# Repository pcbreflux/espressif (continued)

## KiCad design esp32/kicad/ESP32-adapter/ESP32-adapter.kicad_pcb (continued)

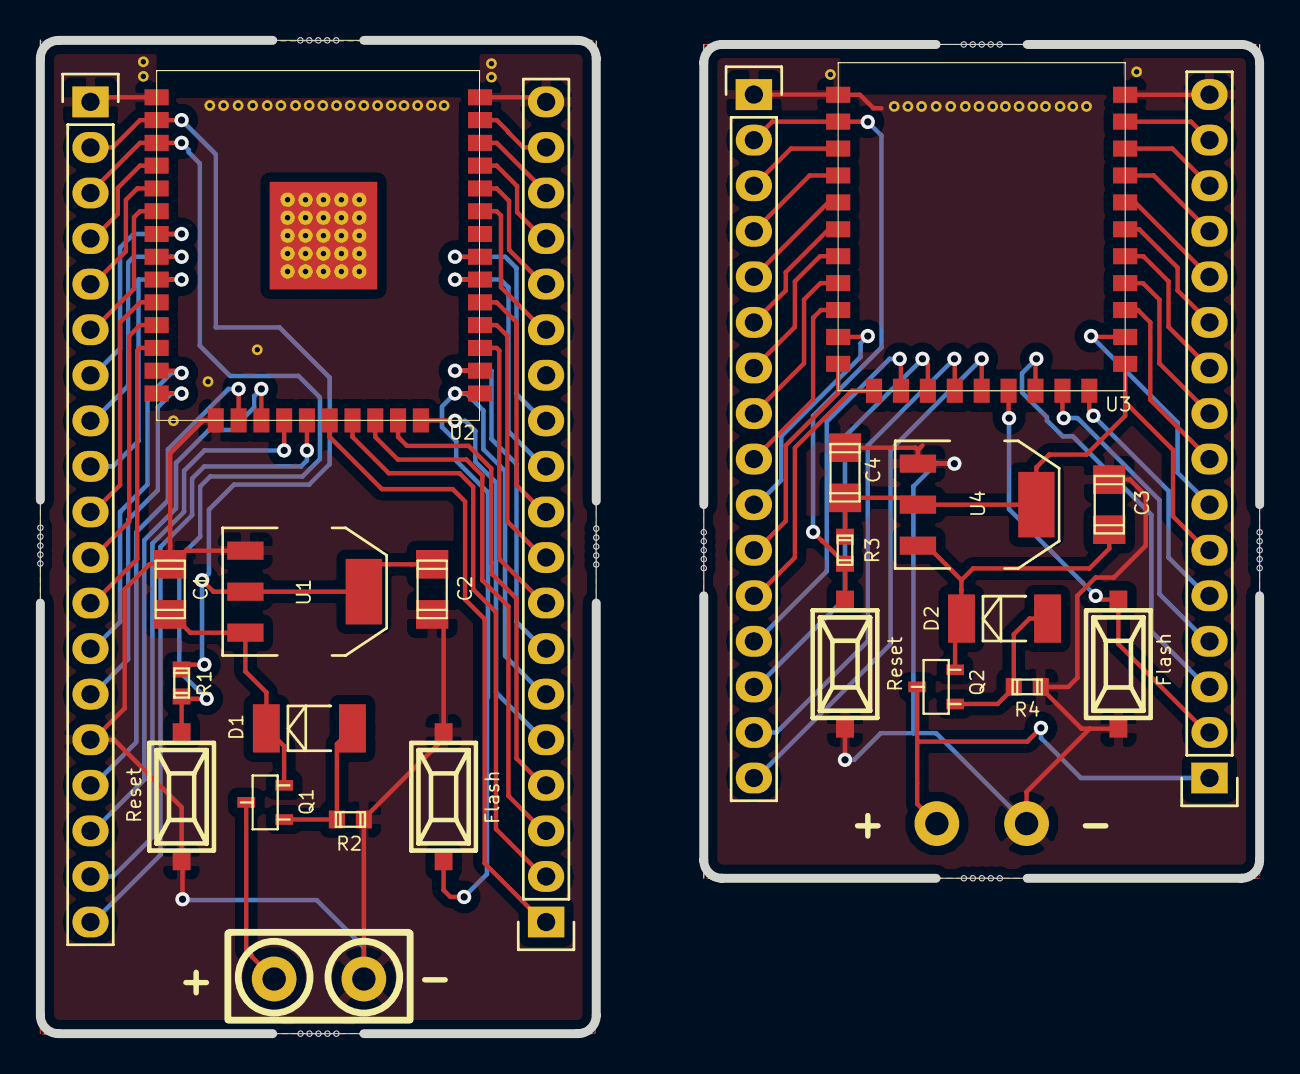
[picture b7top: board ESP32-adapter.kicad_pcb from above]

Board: 2 copper layers, 68.0 x 55.4 mm, 26 parts (1 on the bottom side), 70 nets.

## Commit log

2016-11-06 ESP32 Adapter with KiCad
2016-11-08 ESP32 Eddystone
2016-11-11 iBeacon
2016-11-20 Ucglib ESP32 port
2016-11-30 ESP32 APA102
2016-12-08 ESP32_MAX6675_thingspeak
2016-12-14 ESP32 ssl smtps gmail
2016-12-21 ESP32 u8g2 Si7021 SSD1306
2016-12-27 ESP32 DIY Radar Intrusion Detector
2016-12-30 ESP32 BLE Client with nRF51822 BLE Server
2017-01-03 ESP32 TSL v1.2 Weebserver i.e. GPIO Remetoe Controll
2017-01-04 ESP32-HELP-Button
2017-01-09 ESP32-adapter pinmap
2017-01-09 ESP32-HELP-Button assembly files
2017-01-10 esp-idf changed to bluedroid
2017-01-18 ESP32_blufi_beacon_tracker
2017-01-27 ESP32_mqtt_secure_publish
2017-02-06 ESP32_deep_sleep
2017-02-06 ESP32_mqtt_secure_subscribe (under test)
2017-02-10 ESP32_mqtt_secure_subscribe
2017-02-13 esp-idf update
2017-02-14 issue_321
2017-02-15 ESP32_oled_i2c_u8g2
2017-02-15 Simple C++ Example
2017-02-15 update to lates esp-idf commit
2017-02-21 FreeRTOS inter-task-communication
2017-03-02 Arduino_ESP32_AT
2017-03-09 ESP32 freertos inter task communication
2017-03-10 ESP32_gatts_mqtt_gateway
2017-03-15 ESP32_GPS_Clock
2017-03-17 minmea dwtfyw licence
2017-03-22 ESP32_hall_sensor
2017-03-22 ESP32_int_hall_sensor
2017-03-31 ESP32_bh1750_oled
2017-04-01 ESP32_gattc_demo with new esp-idf
2017-04-02 ESP32_socket_server
2017-04-06 ESP32_gpio_isr
2017-04-08 ESP32_gpio_buzzer
2017-04-08 ESP32_mqtts_sound
2017-04-13 ESP32_gpio_blinky
2017-04-13 ESP32_socket_server_blocking
2017-04-15 ESP32_RFID with NXP MFRC522
2017-04-16 giveaway extractor
2017-04-18 ESP32_RFID
2017-04-19 ESP32_micro-ecc
2017-04-23 ESP32_mqtts_gpio
2017-04-23 ESP32_mqtts
2017-05-02 ESP32_mqtts_apa102
2017-05-05 ESP32_DFPlayer_full
2017-05-05 ESP32-epaper-adapter
2017-05-12 ESP32_Arduino_template
2017-05-14 Giveaway
2017-05-14 ESP32_gpio_WS2812
2017-05-14 ESP32_gpio_apa102
2017-05-24 ESP32_ble_UART
2017-05-26 ESP32_IR_Remote
2017-05-26 ble_app_eddystone
2017-06-05 ESP32_int_temp_sensor
2017-06-09 ESP32_touch
2017-06-13 ESP32_ble_UART with notify
2017-06-14 ESP32_ble_UART with notify and LED
2017-06-14 esp32-at
2017-06-19 ESP32_tasks
2017-06-21 ESP32_DRV8825
2017-06-29 ESP32_AP_upload
2017-06-30 ESP32_deepSleep
2017-07-02 esp32-shopping.ods
2017-07-04 new esp-idf
2017-07-04 update links
2017-07-04 timetable
2017-07-04 esp32-shopping
2017-07-07 ESP32_gattc_demo
2017-07-07 ESP32_eclipse_template
2017-07-11 ESP32_thermo
2017-07-15 ESP32_ble_notify with Neil Kolban CPP Library big thanks for all you work !
2017-07-15 ESP32_ble_i2c_ina219 with Neil Kolban CPP Library big thanks for all you work !
2017-07-16 ESP32_tasks_num
2017-07-17 ESP32_ina219_u8g2
2017-08-04 ESP32_AD8232
2017-08-18 ESP32_ssl_pushbullet
2017-08-25 ESP32-bat-monitor-latch
2017-08-26 ESP32-bat-monitor-latch/
2017-09-06 python mqtt mysql datastore
2017-09-19 ESP32 timer
2017-09-29 ESP32_speed
2017-10-04 ESP32_speed_gpio
2017-10-09 ESP32_gattc_demo update to current esp-idf
2017-10-13 ESP32_blynk_WiFi
2017-10-27 ESP32_Blink_stobe
2017-11-06 ESP32vsESP8266 Arduino Speed and dual core with queues
2017-11-13 slides
2017-11-20 fix issue 25 opened by ujeenator
2017-11-27 ESP32_sd_card
2017-11-29 ESP32_SDCard_Test
2017-12-08 ESP32_blinky34
2017-12-10 Get the openssl https server example to work with new esp-idf toolchain
2017-12-14 ESP32_gatts_mqtt_gateway update to new esp-idf
2017-12-28 ESP32_epaper_u8g2
2018-01-11 ESP32-wroover-adapter
2018-02-02 ESP32_espnow_MasterSlave
2018-02-15 ESP32_BLE_server_UART_Robot
2018-02-20 ESP32_Eddystone_TML_deepsleep
2018-02-28 ESP32_Eddystone_TLM_deepsleep
2018-03-05 ESP32_Eddystone_URL_deepsleep
2018-03-05 ESP32_Eddystone_TML_deepsleep_DHT
2018-03-14 ESP32_BLE_beaconscan
2018-03-15 ESP32_ble_UART new esp-idf
2018-03-21 logo
2018-04-10 ESP32_fingerprint
2018-04-11 ESP32_fingerprint_setup
2018-04-27 ESP32_MQ_Sensor
2018-05-09 ESP32_ArduinoISP
2018-07-04 ESP32-li-ion-cell-monitor
2018-07-30 XDFN8 Footprint flaw
2018-08-09 ESP32_SI7060_INA219
2018-08-19 Remove email address from README.md
    Hi,
    I'm getting email support requests for this project from people who found my email address published in the README (for the ESP-IDF version in use). I'd appreciate it if you please removed it, it's n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
    Thanks,
    Angus
2018-09-20 ESP32-li-ion-cell-monitor Ref1.3
2018-09-20 ESP32_ina226
2018-10-04 ESP32_RotaryEncoder
2018-10-10 ESP32_RotaryEncoderOne
2018-10-12 ESP32_BLE_server_UART_Thinkspeak
2018-10-19 ESP32_BLE_server_UART_Thingspeak
2018-10-19 ESP32_BLE_client_UART
2018-12-12 * proper handling of websocket extended frame (len == 127)
2022-08-23 Fix method name
    rmt_get_ringbuf_handler method changed name to rmt_get_ringbuf_handle
